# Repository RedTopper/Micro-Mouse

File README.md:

# Micromouse (sddec20-28)
This repository contains most of the work done by Senior Design group dec20-28
during the Spring/Fall 2020. 

## Team Members
* Joshua Wooi
* Austin Chesmore
* Aaron Walter
* Richard Anderson
* Tyler Fuchs
* Jorge Gomez

## Website
[sddec20-28.sd.ece.iastate.edu](Senior Design Website)

## Resources
This repository contains additional resources generated during the project.
They are stored inside the `resource` directory in the repository root. The
contents of the folders are as follows:

### resource/alg
A\* and Floodfill Algorithms

This is a standalone implementation of the pathfinding algorithm. You can compile
it with `make`. See the README.md inside this directory for more information

### resource/docs
Documentation Files

This folder contains general information about the project, such as a setup guide,
final report, poster, and anything else documentation wise.

### resource/gui
Past User Interface Files

This directory contains a prototype GUI written in Python. We no longer use it in
favor of a web-based UI, but we will keep it here for archival purposes.

### resource/pcb
Current, Past, and Future PCB Designs

These are the Eagle files used to manufacture the PCB of the robot.

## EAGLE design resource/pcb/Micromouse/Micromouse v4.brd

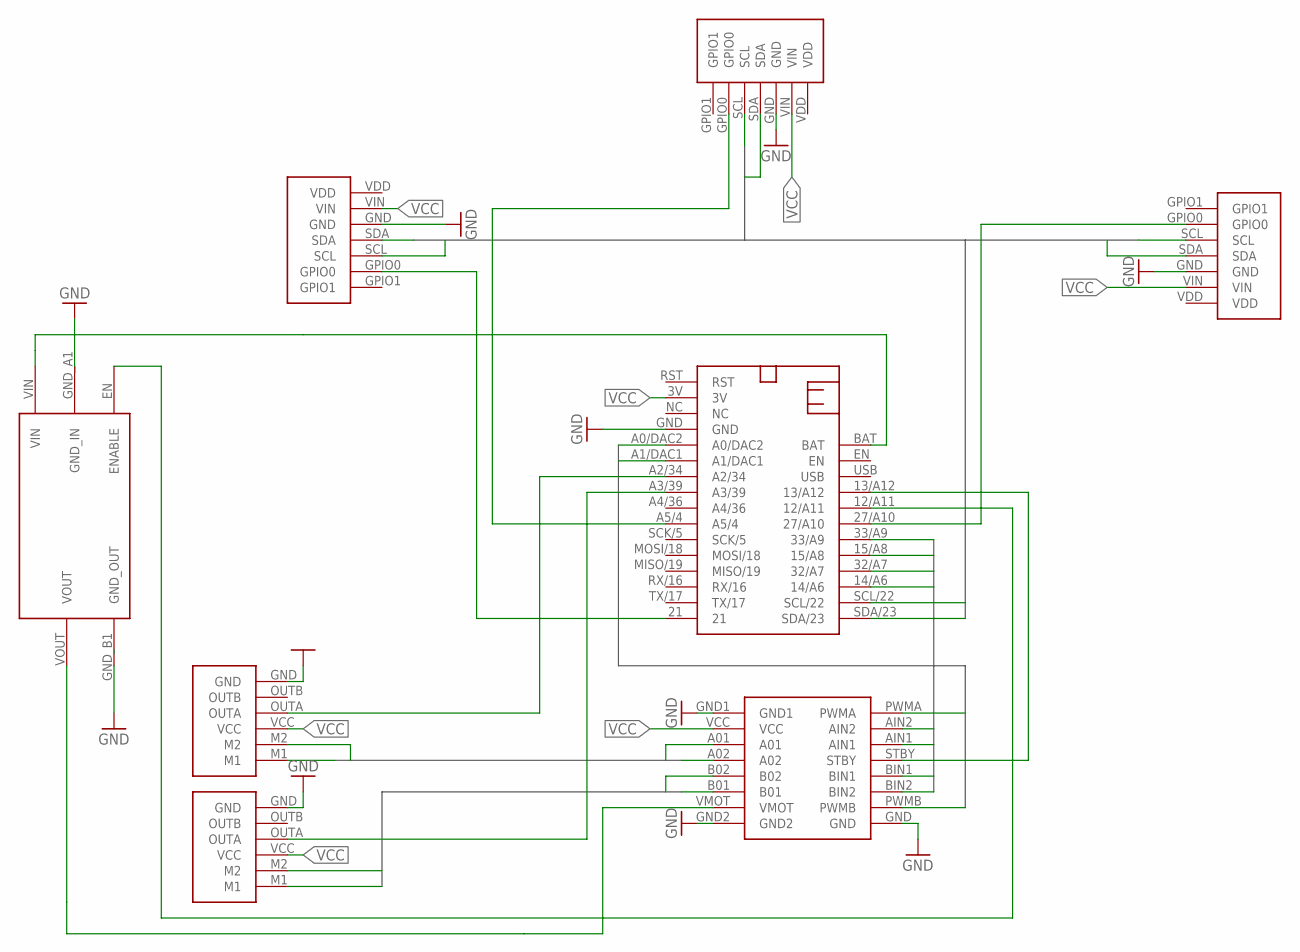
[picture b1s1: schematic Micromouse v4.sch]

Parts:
12V_BOOST: U3V70F12
ENCODE_A2, ENCODE_A3: ENCODE
ESP1: ESP32
MOTOR1: MOTOR
VL_21, VL_27: VL6180-X
VL_A5: VL6180-X

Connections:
AIN1: ESP1.33/A9, MOTOR1.AIN1
AIN2: ESP1.15/A8, MOTOR1.AIN2
BIN1: ESP1.32/A7, MOTOR1.BIN1
BIN2: ESP1.14/A6, MOTOR1.BIN2
BOOST_IN: 12V_BOOST.VIN, ESP1.BAT
BOOST_OUT: 12V_BOOST.VOUT, MOTOR1.VMOT
GND: 12V_BOOST.GND_A1 (GND_IN), 12V_BOOST.GND_B1 (GND_OUT), ENCODE_A2.GND, ENCODE_A3.GND, ESP1.GND, MOTOR1.GND, MOTOR1.GND1, MOTOR1.GND2, VL_21.GND, VL_27.GND, VL_A5.GND
MA1: ENCODE_A2.M1, MOTOR1.A01
MA2: ENCODE_A2.M2, MOTOR1.A02
MB1: ENCODE_A3.M1, MOTOR1.B01
MB2: ENCODE_A3.M2, MOTOR1.B02
unnamed: 12V_BOOST.EN (ENABLE), ESP1.12/A11
unnamed: ESP1.13/A12, MOTOR1.STBY
unnamed: ENCODE_A2.OUTA, ESP1.A2/34
unnamed: ENCODE_A3.OUTA, ESP1.A3/39
unnamed: ESP1.27/A10, VL_27.GPIO0
unnamed: ESP1.21, VL_21.GPIO0
unnamed: ESP1.A5/4, VL_A5.GPIO0
PWMA: ESP1.A1/DAC1, MOTOR1.PWMA
PWMB: ESP1.A0/DAC2, MOTOR1.PWMB
SCL: ESP1.SCL/22, VL_21.SCL, VL_27.SCL, VL_A5.SCL
SDA: ESP1.SDA/23, VL_21.SDA, VL_27.SDA, VL_A5.SDA
VCC: ENCODE_A2.VCC, ENCODE_A3.VCC, ESP1.3V, MOTOR1.VCC, VL_21.VIN, VL_27.VIN, VL_A5.VIN

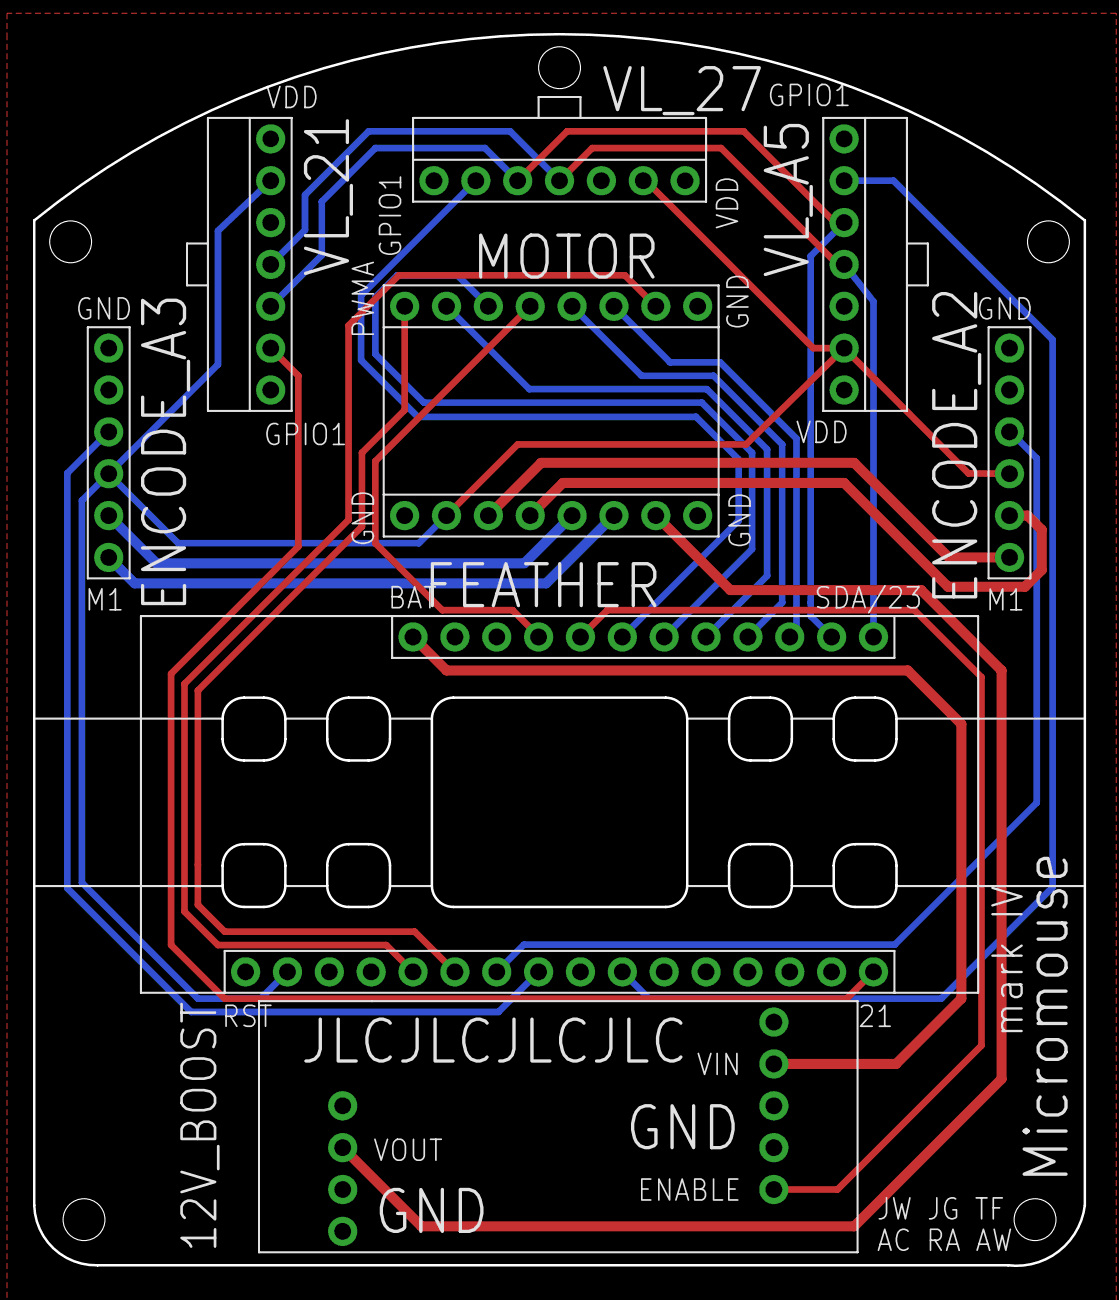
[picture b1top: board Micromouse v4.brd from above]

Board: 2 copper layers, 63.8 x 74.7 mm, 8 parts (0 on the bottom side), 23 nets.

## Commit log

2020-10-08 Make web framework
2020-10-10 Added the sensor
2020-10-14 Create Components
2020-10-14 Add printf.
2020-10-14 Sensor timeout
2020-10-15 fix build error
2020-10-20 rewrite webserver
2020-10-22 Motors
2020-11-05 Sensor init and motor driver
2020-11-06 Make motors work
2020-11-07 Joystick support for wheel speed
2020-11-07 Make robot work
2020-11-12 Signature check
2020-11-15 added alg file
2020-11-15 all but binprint
2020-11-15 started removing mousemap
2020-11-15 Add encoders to code.
2020-11-24 Update some formatting.
2020-11-24 Added GUI files
2020-11-24 Add standalone algorithm files
2020-11-24 Add some documentation files
2020-11-24 Add PCB resources.
2020-11-24 README.md
2020-11-24 Updated PCB
2020-11-24 Added Maze files
2020-11-24 Add Bill of Materials
